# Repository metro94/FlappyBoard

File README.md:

[中文](README_zh.md) | English

# FlappyBoard

## Introduction

A minimum development board for CH32V203G6. The goal is simplicity, convenience and low-cost.

## 3D Rendering View

## License

[CERN-OHL-P](LICENSE)

## EDA

KiCad 6.0.6

## Usages

### Download Programs

It's simple and convenient to use USB download of [WCHISPTool](http://www.wch-ic.com/downloads/WCHISPTool_Setup_exe.html). Also serial download and debug port download is available.

WCHISTool requires correct MCU model (CH32V203) to download. The DIP switch shall be ON for downloading, and power the board with BOOT0 button pushed. If everything goes well, WCHISPTool shall report the MCU.

### LEDs and Buttons

There are two LEDs on the board, including *PWR* for power status (3.3V powered) and *PB8* for user-defined LED.

There are two buttons on the board, including *NRST* for system reset and *BOOT0* for boot mode (the default is to run user program in Flash, and push button to run bootloader in ROM).

> Note: In CH32V203G6, *PB8* and *BOOT0* is multiplexed. The behavior of this pin is:
>
> * When booting, MCU requires *BOOT0* status via this pin, and this pin is input. When *BOOT0* button is pushed, the LED of *PB8* is lighted to hint.
> * After entering user program, the *PB8* pin is available for output only, and the input value is invalid. Now, the LED of *PB8* can be controlled by user program, but the status of *BOOT0* button cannot be read.

### External Clock Input

CH32V203G6 can accept external oscillator and crystal. The valid frequency range is 3-25MHz.

### Schematics

[FlappyBoard Schematic](schematics/FlappyBoard.pdf)

### BOM

[FlappyBoard BOM](https://metro94.github.io/FlappyBoard/bom.html)

### Examples

[software/examples](software/examples)

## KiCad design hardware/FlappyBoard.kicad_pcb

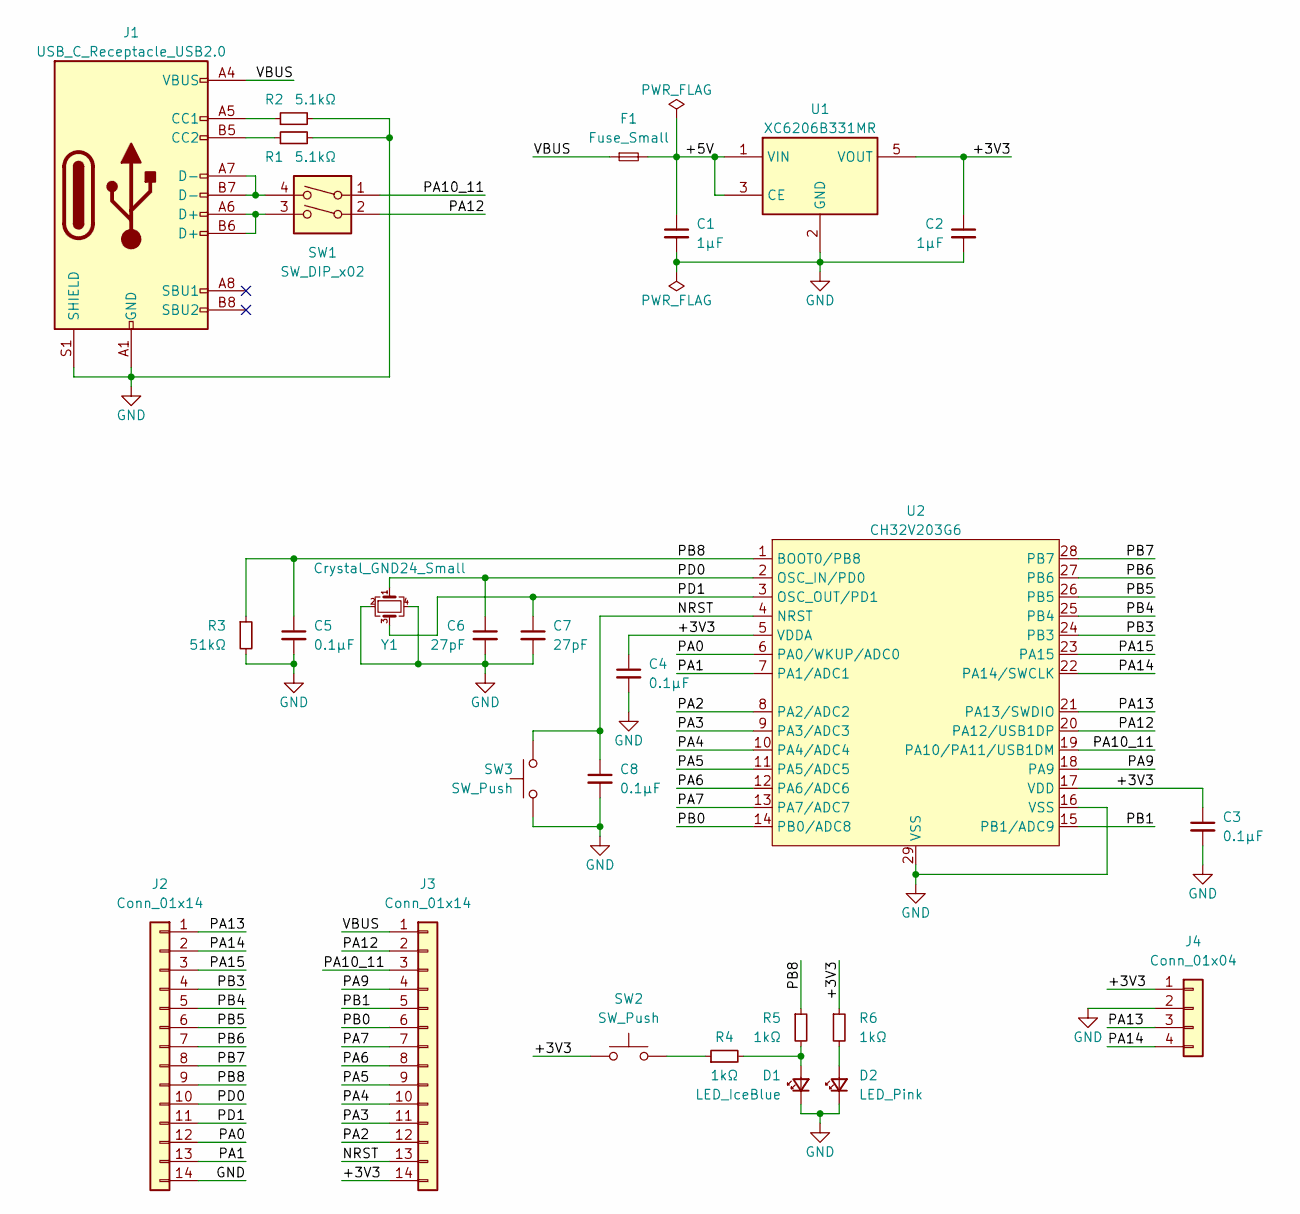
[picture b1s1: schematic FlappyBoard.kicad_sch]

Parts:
C1, C2: 1μF; C_0805_2012Metric; LCSC C28323
C3, C4, C5, C8: 0.1μF; C_0603_1608Metric; LCSC C14663
C6, C7: 27pF; C_0603_1608Metric
D1: LED_IceBlue; LED_0805_2012Metric; LCSC C2892177
D2: LED_Pink; LED_0805_2012Metric; LCSC C2892178
F1: Fuse_Small; Fuse_0805_2012Metric; LCSC C116170
J1: USB_C_Receptacle_USB2.0; USB_C_Receptacle_Palconn_UTC16-G; LCSC C963370
J2, J3: Conn_01x14; Pin_1x14_P2.54mm
J4: Conn_01x04; Pin_1x04_P2.54mm
R1, R2: 5.1kΩ; R_0603_1608Metric; LCSC C23186
R3: 51kΩ; R_0603_1608Metric; LCSC C23196
R4, R5, R6: 1kΩ; R_0603_1608Metric; LCSC C21190
SW1: SW_DIP_x02; SW_DIP_SPSTx02_Slide_Copal_CHS-02B_W7.62mm_P1.27mm; LCSC C3293142
SW2, SW3: SW_Push; SW_Push_1P1T_NO_Vertical_Wuerth_434133025816; LCSC C2888884
U1: XC6206B331MR; SOT-23-5; LCSC C82942
U2: CH32V203G6; QFN-28-1EP_4x4mm_P0.4mm_EP2.3x2.3mm; LCSC C5142280
Y1: Crystal_GND24_Small; Crystal_SMD_3225-4Pin_3.2x2.5mm

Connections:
/+3V3: C2.1, C3.1, C4.1, J3.14, J4.1, R6.1, SW2.1, U1.5 (VOUT), U2.5 (VDDA), U2.17 (VDD)
/+5V: C1.1, F1.2, U1.1 (VIN), U1.3 (CE)
/NRST: C8.1, J3.13, SW3.2, U2.4 (NRST)
/PA0: J2.12, U2.6 (PA0/WKUP/ADC0)
/PA1: J2.13, U2.7 (PA1/ADC1)
/PA2: J3.12, U2.8 (PA2/ADC2)
/PA3: J3.11, U2.9 (PA3/ADC3)
/PA4: J3.10, U2.10 (PA4/ADC4)
/PA5: J3.9, U2.11 (PA5/ADC5)
/PA6: J3.8, U2.12 (PA6/ADC6)
/PA7: J3.7, U2.13 (PA7/ADC7)
/PA9: J3.4, U2.18 (PA9)
/PA10_11: J3.3, SW1.1, U2.19 (PA10/PA11/USB1DM)
/PA12: J3.2, SW1.2, U2.20 (PA12/USB1DP)
/PA13: J2.1, J4.3, U2.21 (PA13/SWDIO)
/PA14: J2.2, J4.4, U2.22 (PA14/SWCLK)
/PA15: J2.3, U2.23 (PA15)
/PB0: J3.6, U2.14 (PB0/ADC8)
/PB1: J3.5, U2.15 (PB1/ADC9)
/PB3: J2.4, U2.24 (PB3)
/PB4: J2.5, U2.25 (PB4)
/PB5: J2.6, U2.26 (PB5)
/PB6: J2.7, U2.27 (PB6)
/PB7: J2.8, U2.28 (PB7)
/PB8: C5.1, J2.9, R3.1, R5.1, U2.1 (BOOT0/PB8)
/PD0: C6.1, J2.10, U2.2 (OSC_IN/PD0), Y1.1
/PD1: C7.1, J2.11, U2.3 (OSC_OUT/PD1), Y1.3
/VBUS: F1.1, J1.A4 (VBUS), J1.A9 (VBUS), J1.B4 (VBUS), J1.B9 (VBUS), J3.1
GND: C1.2, C2.2, C3.2, C4.2, C5.2, C6.2, C7.2, C8.2, D1.1 (K), D2.1 (K), J1.A1 (GND), J1.A12 (GND), J1.B1 (GND), J1.B12 (GND), J1.S1 (SHIELD), J2.14, J4.2, R1.2, R2.2, R3.2, SW3.1, U1.2 (GND), U2.16 (VSS), U2.29 (VSS), Y1.2, Y1.4
unnamed: D1.2 (A), R4.2, R5.2
unnamed: D2.2 (A), R6.2
unnamed: J1.A5 (CC1), R2.1
unnamed: J1.A6 (D+), J1.B6 (D+), SW1.3
unnamed: J1.A7 (D-), J1.B7 (D-), SW1.4
unnamed: J1.B5 (CC2), R1.1
unnamed: R4.1, SW2.2

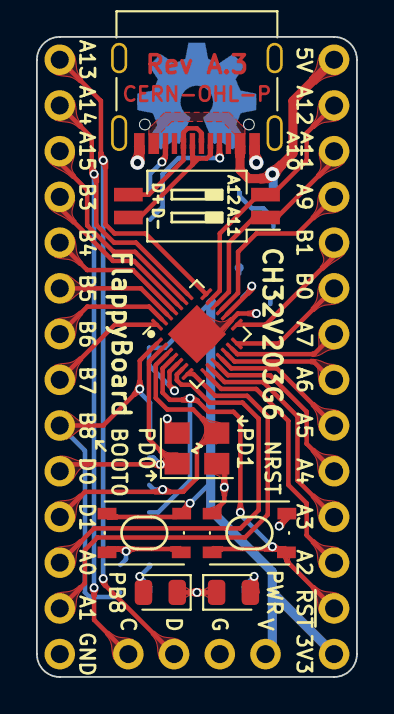
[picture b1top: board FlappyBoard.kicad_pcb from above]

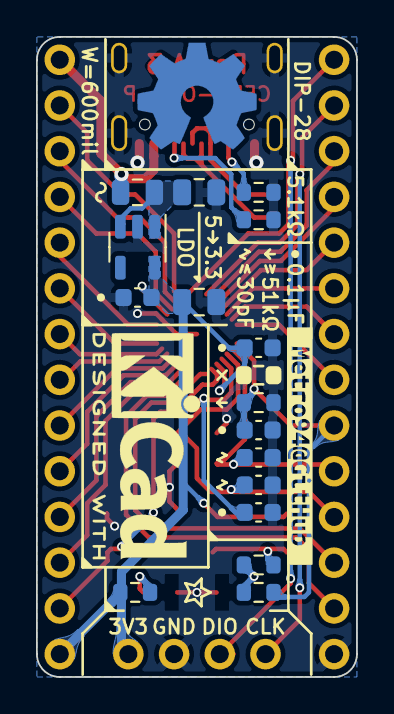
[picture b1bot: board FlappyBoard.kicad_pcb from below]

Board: 2 copper layers, 17.8 x 35.6 mm, 28 parts (17 on the bottom side), 36 nets.

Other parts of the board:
kibuzzard-6318E6BD: G***; kibuzzard-6318E6BD

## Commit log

2022-09-24 Rev A.3 released
2022-09-24 Add description for examples
2022-09-24 Add CompositeKM example
2022-09-25 Modify attributes for hex file
